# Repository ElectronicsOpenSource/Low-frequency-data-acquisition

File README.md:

# Low-frequency-data-acquisition
A board design with example code for data acquisition with 14-, 16-, or 18-bit resolution at 100 up to 1000 kSPS

# For more information visit OSPESA on google groups
https://groups.google.com/forum/#!forum/ospesa

Supported ADCs (to be tested):
These are all the ADCs that should be supported. The footprint used is the 10-MSOP. All ADCs are either differential or pseudo-differential (check for your application).

14-bit  -  250 kSPS  -  AD7942    -  ~$12 ea.

14-bit  -  500 kSPS  -  AD7946    -  ~$16 ea.

16-bit  -  100 kSPS  -  AD7988-1  -  ~$17 ea.

16-bit  -  250 kSPS  -  AD7685    -  ~$14 ea.     <--- I used these for now

16-bit  -  250 kSPS  -  AD7687    -  ~$19 ea.

16-bit  -  500 kSPS  -  AD7686    -  ~$24 ea.

16-bit  -  500 kSPS  -  AD7688    -  ~$29 ea.

16-bit  -  500 kSPS  -  AD7693    -  ~$35 ea.

16-bit  -  500 kSPS  -  AD7988-5  -  ~$17 ea.

16-bit  -  1000 kSPS  -  AD7980   -  ~$23 ea.

16-bit  -  1000 kSPS  -  AD7983   -  ~$34 ea.

18-bit  -  100 kSPS  -  AD7989-1  -  ~$19 ea.

18-bit  -  250 kSPS  -  AD7691    -  ~$28 ea.

18-bit  -  500 kSPS  -  AD7690    -  ~$38 ea.

18-bit  -  500 kSPS  -  AD7989-5  -  ~$25 ea.

18-bit  -  1000 kSPS  -  AD7982   -  ~$41 ea.

18-bit  -  1000 kSPS  -  AD7984   -  ~$50 ea

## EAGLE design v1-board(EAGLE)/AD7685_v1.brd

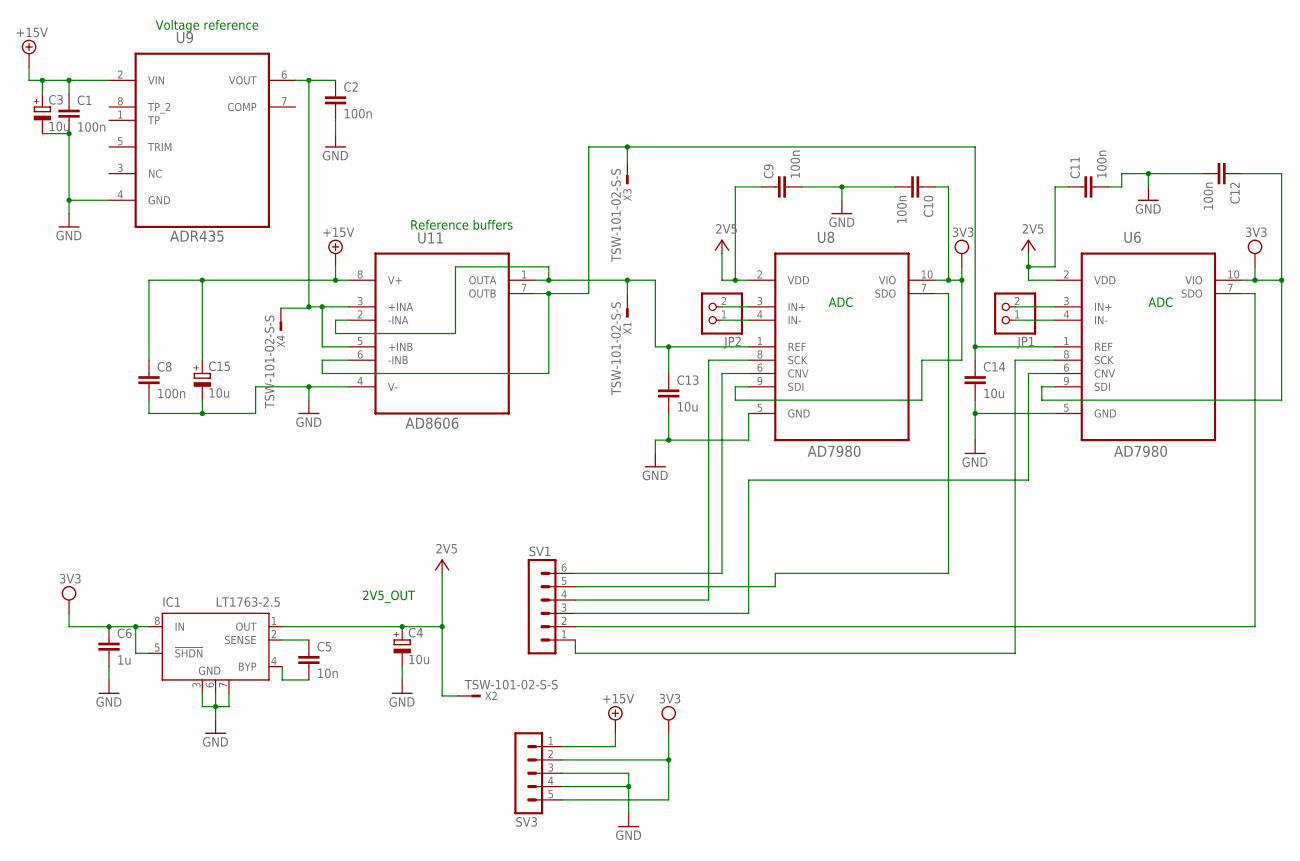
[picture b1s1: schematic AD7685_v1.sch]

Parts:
C1, C2, C8, C9, C10, C11, C12: 100n; C0603K
C3, C4, C15: 10u; SMC_A
C5: 10n; C0603K
C6: 1u; C0603K
C13, C14: 10u; C0603K
IC1: LT1763-2.5; SOIC8
JP1, JP2: PINHD-1X2; 1X02
SV1: MA06-1
SV3: MA05-1
U6, U8: AD7980; SOP50P490X110-10N
U9: ADR435; SOP65P490X110-8N
U11: AD8606; SOP65P490X110-8N
X1, X2, X3, X4: TSW-101-02-S-S

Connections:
+15V: C1.1, C3.+, C8.1, C15.+, SV3.1, U9.2 (VIN), U11.8 (V+)
COMP: U9.7 (COMP)
GND: C1.2, C2.2, C3.-, C4.-, C6.2, C8.2, C9.2, C10.2, C11.2, C12.2, C13.2, C14.2, C15.-, IC1.3 (GND), IC1.6 (GND), IC1.7 (GND), SV3.3, SV3.4, U6.5 (GND), U8.5 (GND), U9.4 (GND), U11.4 (V-)
unnamed: JP2.2, U8.3 (IN+)
unnamed: JP2.1, U8.4 (IN-)
unnamed: SV1.4, U8.8 (SCK)
unnamed: C5.2, IC1.4 (BYP)
unnamed: C5.1, IC1.2 (SENSE)
unnamed: JP1.2, U6.3 (IN+)
unnamed: C2.1, U9.6 (VOUT), U11.3 (+INA), U11.5 (+INB), X4.1
unnamed: SV1.6, U8.6 (CNV)
unnamed: C14.1, U6.1 (REF), U11.6 (-INB), U11.7 (OUTB), X3.1
unnamed: JP1.1, U6.4 (IN-)
unnamed: SV1.5, U8.7 (SDO)
unnamed: C13.1, U8.1 (REF), U11.1 (OUTA), U11.2 (-INA), X1.1
unnamed: SV1.1, U6.8 (SCK)
unnamed: SV1.3, U6.6 (CNV)
unnamed: SV1.2, U6.7 (SDO)
V+: C4.+, C9.1, C11.1, IC1.1 (OUT), U6.2 (VDD), U8.2 (VDD), X2.1
VDD: C6.1, C10.1, C12.1, IC1.5 (!SHDN), IC1.8 (IN), SV3.2, SV3.5, U6.9 (SDI), U6.10 (VIO), U8.9 (SDI), U8.10 (VIO)

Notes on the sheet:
Reference buffers
Voltage reference
ADC
2V5_OUT

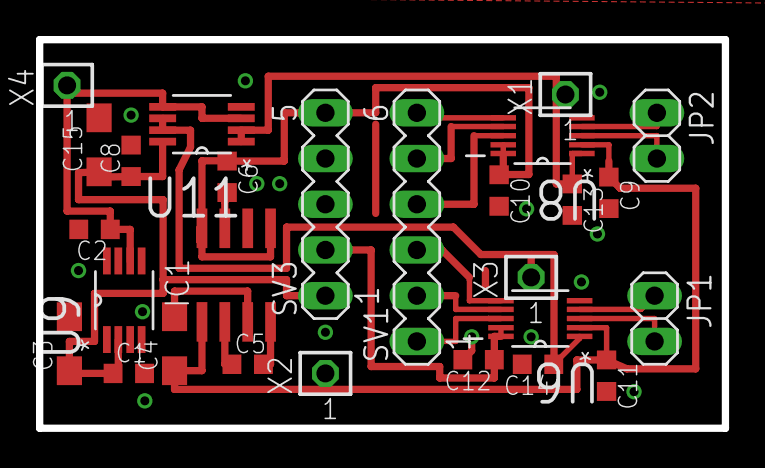
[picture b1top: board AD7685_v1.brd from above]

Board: 2 copper layers, 38.1 x 21.6 mm, 27 parts (0 on the bottom side), 19 nets.

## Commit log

2015-01-19 Added these for documentation purposes only
2015-01-19 Schematic, board layout and Gerber files
2015-01-20 VHDL code to test the AD7865 ADC at 250 kSPS
    Uses a 20 MHz clock to achieve 250 kSPS
    8192 samples are read and then output to a PC via RS232
